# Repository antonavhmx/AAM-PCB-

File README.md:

# 🚀 Sistema Embebido STM32 & PMIC - Diseño PCB de 4 Capas (HDI)

Este repositorio contiene el diseño de hardware y los archivos de manufactura industrial para una tarjeta de circuito impreso de 4 capas. El proyecto se centra en la integración de un microcontrolador de alto rendimiento y gestión de energía, aplicando técnicas de interconexión de alta densidad.

## 📸 Vistas del Proyecto

### Ruteo de Alta Densidad (Layout 2D)

*Detalle del ruteo multicapa mostrando el abanico de salida del BGA, conexiones del PMIC y gestión de tolerancias DRC.*

### Renderizado 3D (Ensamblaje)
**Capa Superior (Top):**

**Capa Inferior (Bottom):**

## ⚙️ Especificaciones Técnicas

*   **Stackup:** 4 Capas (Capa Superior, Plano GND, Plano VCC, Capa Inferior).
*   **Tecnología HDI:** Implementación de reglas de interconexión de alta densidad para encapsulados complejos.
*   **Procesamiento:** Microcontrolador STM32 en encapsulado BGA.
*   **Gestión de Energía:** PMIC integrado para la regulación eficiente de voltajes.
*   **Reglas de Manufactura (DRC):**
    *   Aplicación estricta de *Via-in-Pad* (0.15mm) para maximizar el espacio y garantizar la integridad de las señales.
    *   Ajuste de impedancias, anchos de pista y aislamientos para asegurar la viabilidad de manufactura sin cortocircuitos.

## 🛠️ Herramientas Utilizadas

*   **KiCad:** Layout de PCB, validación de reglas de diseño (DRC) y generación de visualizaciones 3D.
*   **Git / GitHub:** Control de versiones del hardware y respaldo en la nube del paquete de manufactura.

## 📁 Estructura del Repositorio

*   `/aam_bom_pcb/`: Archivos fuente del proyecto de KiCad (esquemático, PCB, archivos de reglas de diseño).
*   `/gerbers/`: Paquete de manufactura industrial empaquetado (Archivos Gerber X2 y taladros Excellon Drill), validado y listo para fabricación y ensamble (PCBA).

---
## 👥 Créditos y Equipo de Trabajo

Este proyecto de hardware fue desarrollado de manera colaborativa, dividiendo el diseño lógico de la implementación física:

*   **Nava Hernández José Antonio**: Autoría intelectual del proyecto, diseño de la lógica del sistema y captura del esquemático original.
*   **Emilio Severo Bernal López**: Ruteo y layout de la PCB (4 capas con tecnología HDI), validación de reglas de manufactura (DRC) y generación del paquete industrial (Gerber/Drill).

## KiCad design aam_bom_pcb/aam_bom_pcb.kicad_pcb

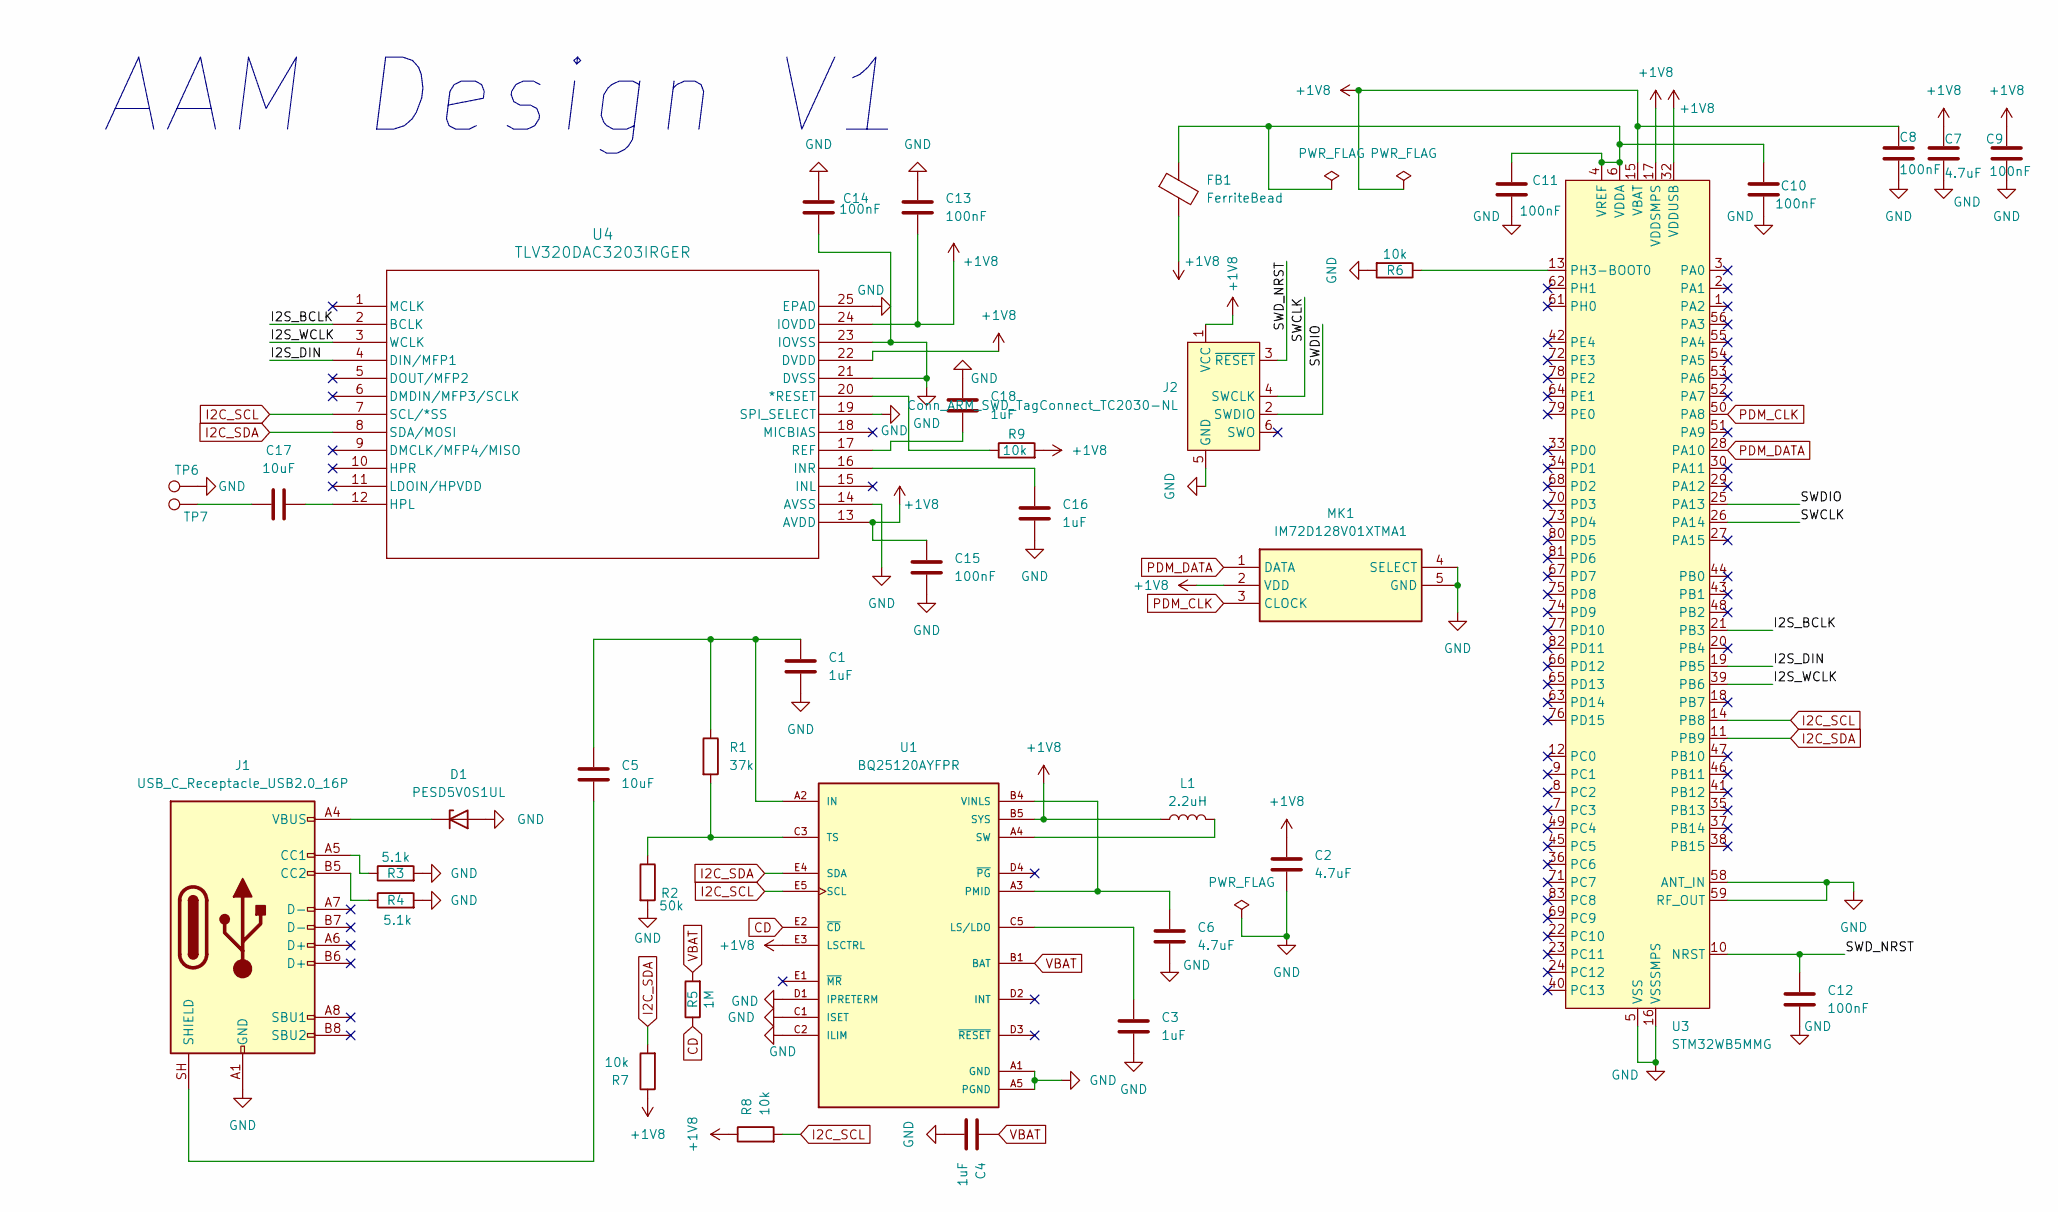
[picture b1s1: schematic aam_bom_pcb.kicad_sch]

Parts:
C1, C3, C4, C16, C18: 1uF; C_0402_1005Metric
C2, C6, C7: 4.7uF; C_0402_1005Metric
C5, C17: 10uF; C_0402_1005Metric
C8, C9, C10, C11, C12, C13, C14, C15: 100nF; C_0402_1005Metric
D1: PESD5V0S1UL; D_SOD-882
FB1: FerriteBead; L_0402_1005Metric
J1: USB_C_Receptacle_USB2.0_16P; USB_C_Receptacle_HCTL_HC-TYPE-C-16P-01A
J2: Conn_ARM_SWD_TagConnect_TC2030-NL; Tag-Connect_TC2030-IDC-NL_2x03_P1.27mm_Vertical
L1: 2.2uH; L_1008_2520Metric
MK1: IM72D128V01XTMA1; Mouser Part Number 726-IM72D128V01XTMA1
R1: 37k; R_0402_1005Metric
R2: 50k; R_0402_1005Metric
R3, R4: 5.1k; R_0402_1005Metric
R5: 1M; R_0402_1005Metric
R6, R7, R8, R9: 10k; R_0402_1005Metric
TP6, TP7: TestPoint; TestPoint_Pad_1.5x1.5mm
U1: BQ25120AYFPR; IC_BQ25120AYFPR; PARTREV A
U3: STM32WB5MMG; ST-SiP-LGA-86-11x7.3mm
U4: TLV320DAC3203IRGER; RGE24_2P7X2P7_TEX

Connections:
+1V8: C2.1, C7.1, C8.1, C9.1, C13.2, C15.1, FB1.2, J2.1 (VCC), L1.1, MK1.2 (VDD), R7.1, R8.1, R9.2, U1.B5 (SYS), U1.E3 (LSCTRL), U3.15 (VBAT), U3.17 (VDDSMPS), U3.32 (VDDUSB), U4.13 (AVDD), U4.22 (DVDD), U4.24 (IOVDD)
/I2S_BCLK: U3.21 (PB3), U4.2 (BCLK)
/I2S_DIN: U3.19 (PB5), U4.4 (DIN/MFP1)
/I2S_WCLK: U3.39 (PB6), U4.3 (WCLK)
/SWCLK: J2.4 (SWCLK), U3.26 (PA14)
/SWDIO: J2.2 (SWDIO), U3.25 (PA13)
/SWD_NRST: C12.1, J2.3 (~RESET), U3.10 (NRST)
CD: R5.1, U1.E2 (~CD)
GND: C1.2, C2.2, C3.2, C4.2, C6.2, C7.2, C8.2, C9.2, C10.2, C11.2, C12.2, C13.1, C14.1, C14.2, C15.2, C16.2, C18.1, D1.2 (A), J1.A1 (GND), J1.A12 (GND), J1.B1 (GND), J1.B12 (GND), J2.5 (GND), MK1.4 (SELECT), MK1.5 (GND), R2.2, R3.2, R4.2, R6.2, TP6.1 (1_1), U1.A1 (GND), U1.A5 (PGND), U1.C1 (ISET), U1.C2 (ILIM), U1.D1 (IPRETERM), U1.D5 (GND), U3.5 (VSS), U3.16 (VSSSMPS), U3.31 (VSS), U3.57 (VSS), U3.58 (ANT_IN), U3.59 (RF_OUT), U3.60 (VSS), U3.84 (VSS), U3.86 (VSS), U4.14 (AVSS), U4.19 (SPI_SELECT), U4.21 (DVSS), U4.23 (IOVSS), U4.25 (EPAD); also elsewhere on the board
I2C_SCL: R8.2, U1.E5 (SCL), U3.14 (PB8), U4.7 (SCL/*SS)
I2C_SDA: R7.2, U1.E4 (SDA), U3.11 (PB9), U4.8 (SDA/MOSI)
unnamed: C6.1, U1.A3 (PMID), U1.B3 (PMID), U1.B4 (VINLS), U1.C4 (VINLS)
unnamed: C17.1, TP7.1 (1_1)
unnamed: D1.1 (K), J1.A4 (VBUS), J1.A9 (VBUS), J1.B4 (VBUS), J1.B9 (VBUS)
unnamed: J1.A5 (CC1), R3.1
unnamed: J1.B5 (CC2), R4.1
unnamed: C5.2, J1.SH (SHIELD)
unnamed: C1.1, C5.1, R1.1, U1.A2 (IN)
unnamed: C3.1, U1.C5 (LS/LDO)
unnamed: L1.2, U1.A4 (SW)
unnamed: R1.2, R2.1, U1.C3 (TS)
unnamed: R6.1, U3.13 (PH3-BOOT0)
unnamed: C10.1, C11.1, FB1.1, U3.4 (VREF), U3.6 (VDDA)
unnamed: R9.1, U4.20 (*RESET)
unnamed: C17.2, U4.12 (HPL)
unnamed: C16.1, U4.16 (INR)
unnamed: C18.2, U4.17 (REF)
PDM_CLK: MK1.3 (CLOCK), U3.50 (PA8)
PDM_DATA: MK1.1 (DATA), U3.28 (PA10)
VBAT: C4.1, R5.2, U1.B1 (BAT), U1.B2 (BAT)

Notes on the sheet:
AAM Design V1

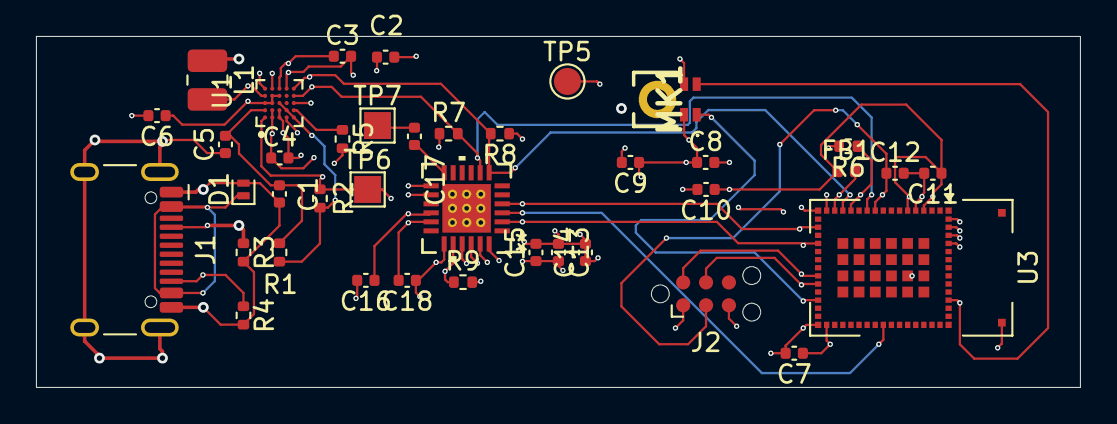
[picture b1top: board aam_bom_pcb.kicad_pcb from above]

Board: 4 copper layers, 58.0 x 19.5 mm, 39 parts (0 on the bottom side), 30 nets.

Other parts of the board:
TP5: TestPoint; TestPoint_Pad_D1.5mm

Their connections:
GND: TP5.1 (1_1); also elsewhere on the board
